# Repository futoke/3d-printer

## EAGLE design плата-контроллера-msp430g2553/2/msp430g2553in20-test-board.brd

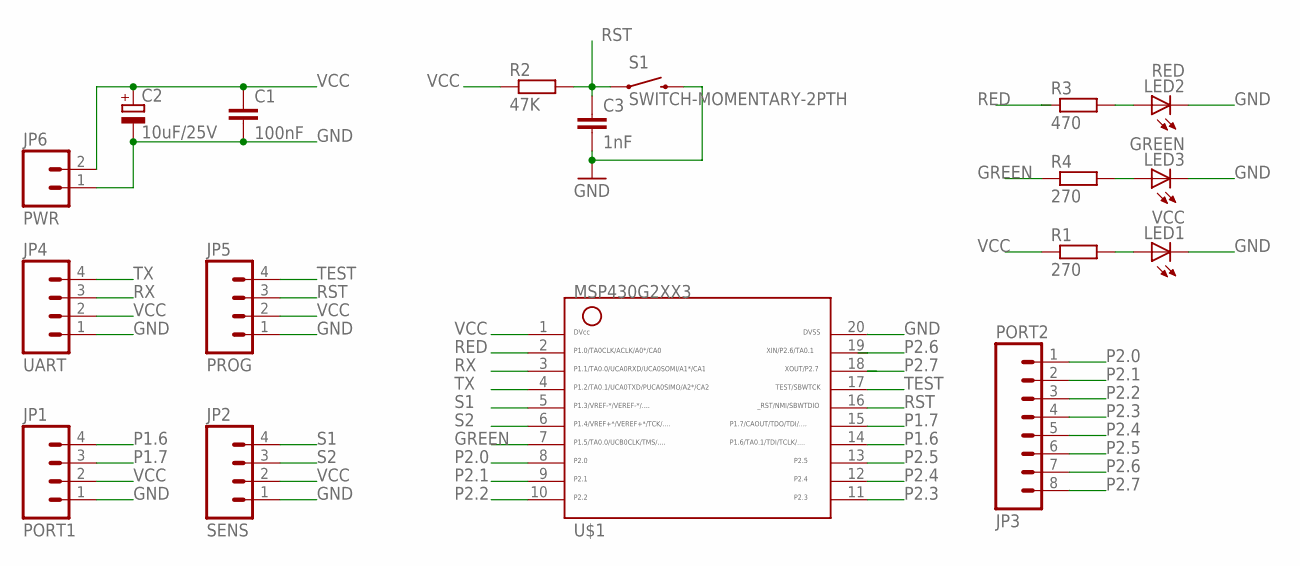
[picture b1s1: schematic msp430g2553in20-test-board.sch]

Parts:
C1: 100nF; C025-025X050
C2: 10uF/25V; E2-5
C3: 1nF; C025-025X050
JP1: PORT1; 1X04
JP2: SENS; 1X04
JP3: PORT2; 1X08
JP4: UART; 1X04
JP5: PROG; 1X04
JP6: PWR; MOLEX-1X2
LED1: VCC; LED3MM
LED2: RED; LED3MM
LED3: GREEN; LED3MM
R1, R4: 270; 0204/5
R2: 47K; 0204/5
R3: 470; 0204/5
S1: SWITCH-MOMENTARY-2PTH; TACTILE-PTH
U$1: G2XX3---N20; N20

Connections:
GND: C1.2, C2.-, C3.2, JP1.1, JP2.1, JP4.1, JP5.1, JP6.1, LED1.K (C), LED2.K (C), LED3.K (C), S1.3 (2), U$1.20
GREEN: R4.1, U$1.7
unnamed: LED3.A, R4.2
unnamed: LED1.A, R1.2
unnamed: LED2.A, R3.2
P1.6: JP1.4, U$1.14
P1.7: JP1.3, U$1.15
P2.0: JP3.1, U$1.8
P2.1: JP3.2, U$1.9
P2.2: JP3.3, U$1.10
P2.3: JP3.4, U$1.11
P2.4: JP3.5, U$1.12
P2.5: JP3.6, U$1.13
P2.6: JP3.7, U$1.19
P2.7: JP3.8, U$1.18
RED: R3.1, U$1.2
RST: C3.1, JP5.3, R2.2, S1.1, U$1.16
RX: JP4.3, U$1.3
S1: JP2.4, U$1.5
S2: JP2.3, U$1.6
TEST: JP5.4, U$1.17
TX: JP4.4, U$1.4
VCC: C1.1, C2.+, JP1.2, JP2.2, JP4.2, JP5.2, JP6.2, R1.1, R2.1, U$1.1

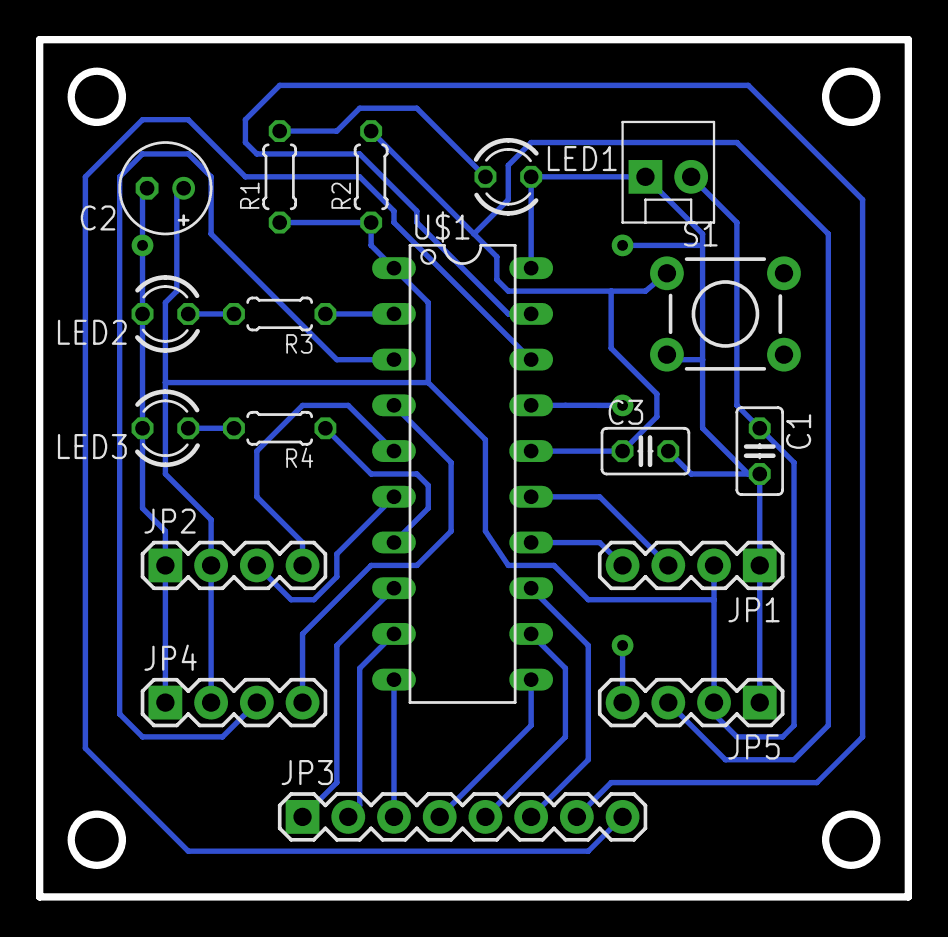
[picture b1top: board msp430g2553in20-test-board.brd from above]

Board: 2 copper layers, 48.3 x 47.6 mm, 18 parts (0 on the bottom side), 23 nets.

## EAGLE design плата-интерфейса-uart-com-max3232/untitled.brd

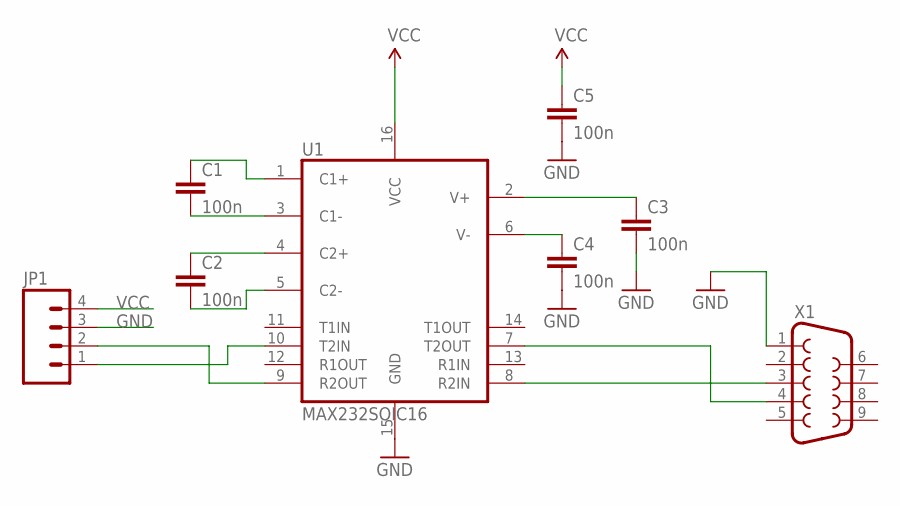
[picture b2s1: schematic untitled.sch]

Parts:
C1, C2, C3, C4, C5: 100n; 1206
JP1: M04PTH; 1X04
U1: MAX232SOIC16; SO016
X1: DB9FEMALE; DB9

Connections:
GND: C3.2, C4.2, C5.2, JP1.3, U1.15 (GND), X1.1
unnamed: C1.1, U1.1 (C1+)
unnamed: C1.2, U1.3 (C1-)
unnamed: C2.1, U1.4 (C2+)
unnamed: C2.2, U1.5 (C2-)
unnamed: C3.1, U1.2 (V+)
unnamed: C4.1, U1.6 (V-)
unnamed: U1.8 (R2IN), X1.3
unnamed: U1.7 (T2OUT), X1.4
unnamed: JP1.2, U1.9 (R2OUT)
unnamed: JP1.1, U1.10 (T2IN)
VCC: C5.1, JP1.4, U1.16 (VCC)

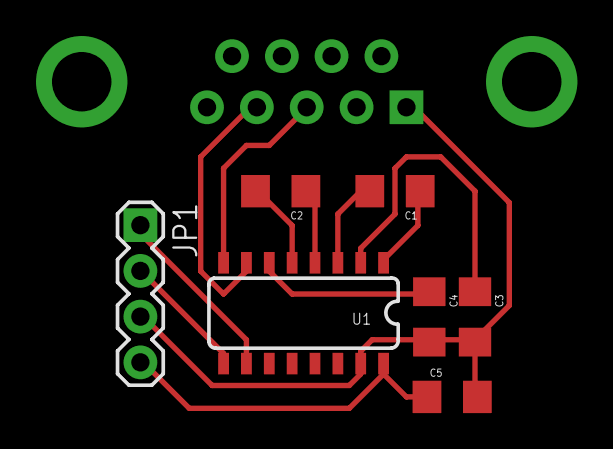
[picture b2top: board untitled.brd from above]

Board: 2 copper layers, 8 parts (1 on the bottom side), 12 nets.

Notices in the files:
parts and their libraries:
SparkFun-DigitalIC: Licensing: CC v3.0 Share-Alike You are welcome to use this library for commercial purposes.
